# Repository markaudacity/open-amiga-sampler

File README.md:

# *ghOASt: a spectre is haunting open-source retro sampling*

## Open source schematics, parts lists and documentation for building a generic 8bit/mono Amiga parallel port sound sampler

*note: the following info is from the original repo and I claim no credit for it* 

Amiga parallel port sound samplers are simple hardware devices from the late 80s/early 90s which allowed users to digitally record audio to their home computer and represented a revolution in DIY music production. They were once cheap and ubiquitous, but they're increasingly expensive and hard to find as the popularity of retro computing continues to rise.

OAS is an open source PCB and case design for a cartridge-style mono sampler geared towards use with Soundtracker and Protracker-style software. It is easy to make, cheap to produce, and thanks to its built in preamp with hardware gain control it can deliver higher quality results than the average vintage sampler.

Check out the Wiki for answers to most hardware questions:
## [OAS Wiki](https://github.com/echolevel/open-amiga-sampler/wiki)

### Background
***
* [What are Amiga samplers?](https://github.com/echolevel/open-amiga-sampler/wiki/What-are-Amiga-samplers%3F)
* [Why build more?](https://github.com/echolevel/open-amiga-sampler/wiki/Why-build-more%3F)

### Development

***
* [How do they work?](https://github.com/echolevel/open-amiga-sampler/wiki/How-do-they-work%3F)
* [⚠️ WARNING](https://github.com/echolevel/open-amiga-sampler/wiki/%E2%9A%A0%EF%B8%8F-WARNING)
* [That WARNING sounds serious. How did you test your design without risking Amiga hardware?](https://github.com/echolevel/open-amiga-sampler/wiki/That-WARNING-sounds-serious.-How-did-you-test-your-design-without-risking-your-Amiga-hardware%3F)
* [Why is this sampler design mono, not stereo?](https://github.com/echolevel/open-amiga-sampler/wiki/Why-is-this-sampler-design-mono,-not-stereo%3F)
* [What's the aim in terms of quality and application?](https://github.com/echolevel/open-amiga-sampler/wiki/What's-the-aim-in-terms-of-quality-and-application%3F)
* [What about those edge cases? Who is OAS not aimed at?](https://github.com/echolevel/open-amiga-sampler/wiki/What-about-those-edge-cases%3F-Who-is-OAS-not-aimed-at%3F)
* [How compatible is OAS with existing software? (Work in progress, submissions welcome)](https://github.com/echolevel/open-amiga-sampler/wiki/How-compatible-is-OAS-with-existing-software%3F-(Work-in-progress,-submissions-welcome))
* [Current status](https://github.com/echolevel/open-amiga-sampler/wiki/Current-status)

### Production & Availability

***
* [Availability](https://github.com/echolevel/open-amiga-sampler/wiki/Availability)
* [DIY assembly](https://github.com/echolevel/open-amiga-sampler/wiki/DIY-assembly)

### Appendices

***
* [Appendix A: Sample rates deep-dive](https://github.com/echolevel/open-amiga-sampler/wiki/Appendix-A:-Sample-rates-deep-dive)
* [Appendix B: Sampling duration deep-dive](https://github.com/echolevel/open-amiga-sampler/wiki/Appendix-B:-Sampling-duration-deep-dive)

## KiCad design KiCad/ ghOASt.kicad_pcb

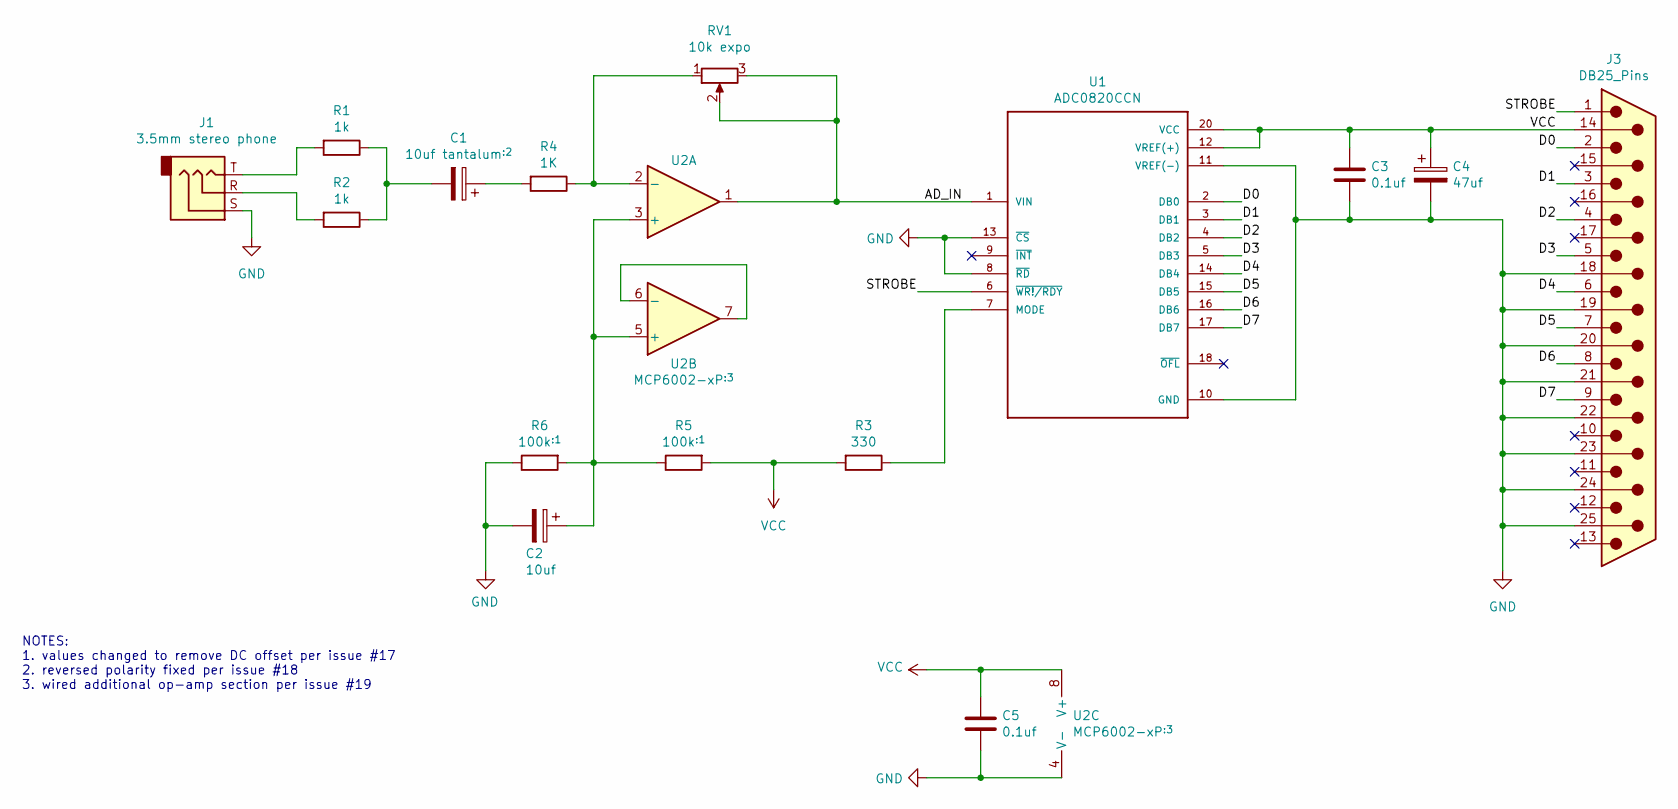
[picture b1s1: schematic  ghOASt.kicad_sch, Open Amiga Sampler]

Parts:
C1: 10uf tantalum^{:2}; CP_Radial_D4.0mm_P1.50mm
C2: 10uf; CP_Radial_D4.0mm_P1.50mm
C3, C5: 0.1uf; C_Disc_D4.3mm_W1.9mm_P5.00mm
C4: 47uf; CP_Radial_D4.0mm_P1.50mm
J1: 3.5mm stereo phone; Jack_3.5mm_CUI_SJ1-3543
J3: DB25_Pins; DSUB-25_Male_EdgeMount_P2.77mm
R1, R2: 1k; R_Axial_DIN0207_L6.3mm_D2.5mm_P10.16mm_Horizontal
R3: 330; R_Axial_DIN0207_L6.3mm_D2.5mm_P10.16mm_Horizontal
R4: 1K; R_Axial_DIN0207_L6.3mm_D2.5mm_P10.16mm_Horizontal
R5, R6: 100k^{:1}; R_Axial_DIN0207_L6.3mm_D2.5mm_P10.16mm_Horizontal
RV1: 10k expo; Potentiometer_Alpha_RD901F-40-00D_Single_Vertical
U1: ADC0820CCN; DIP-20_W7.62mm_Socket
U2: MCP6002-xP^{:3}; DIP-8_W7.62mm_Socket

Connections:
/AD_IN: RV1.2, RV1.3, U1.1 (VIN), U2.1
/D0: J3.2, U1.2 (DB0)
/D1: J3.3, U1.3 (DB1)
/D2: J3.4, U1.4 (DB2)
/D3: J3.5, U1.5 (DB3)
/D4: J3.6, U1.14 (DB4)
/D5: J3.7, U1.15 (DB5)
/D6: J3.8, U1.16 (DB6)
/D7: J3.9, U1.17 (DB7)
/STROBE: J3.1, U1.6 (~WR!/RDY)
GND: C2.2, C3.2, C4.2, C5.2, J1.S, J3.18, J3.19, J3.20, J3.21, J3.22, J3.23, J3.24, J3.25, R6.1, U1.8 (~RD), U1.10 (GND), U1.11 (VREF(-)), U1.13 (~CS), U2.4 (V-)
unnamed: C1.1, R4.2
unnamed: C1.2, R1.1, R2.1
unnamed: J1.R, R2.2
unnamed: J1.T, R1.2
unnamed: R3.1, U1.7 (MODE)
unnamed: C2.1, R5.1, R6.2, U2.3 (+), U2.5 (+)
unnamed: R4.1, RV1.1, U2.2 (-)
unnamed: U2.6 (-), U2.7
VCC: C3.1, C4.1, C5.1, J3.14, R3.2, R5.2, U1.12 (VREF(+)), U1.20 (VCC), U2.8 (V+)

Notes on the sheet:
NOTES: 1. values changed to remove DC offset per issue #17 2. reversed polarity fixed per issue #18 3. wired additional op-amp section per issue #19

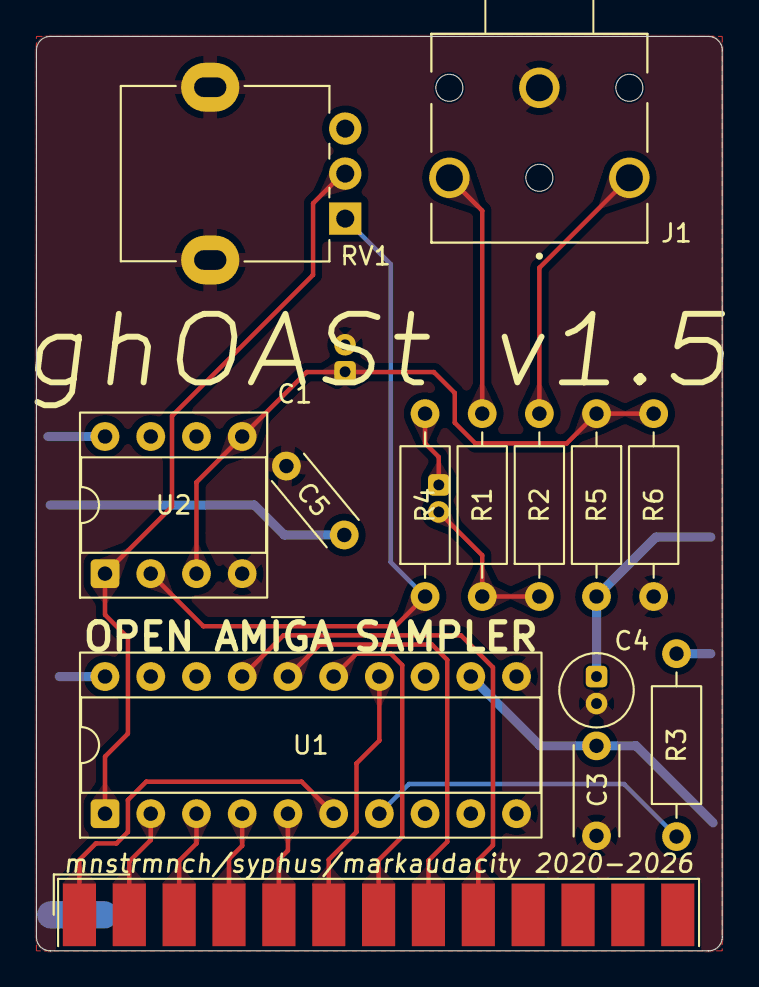
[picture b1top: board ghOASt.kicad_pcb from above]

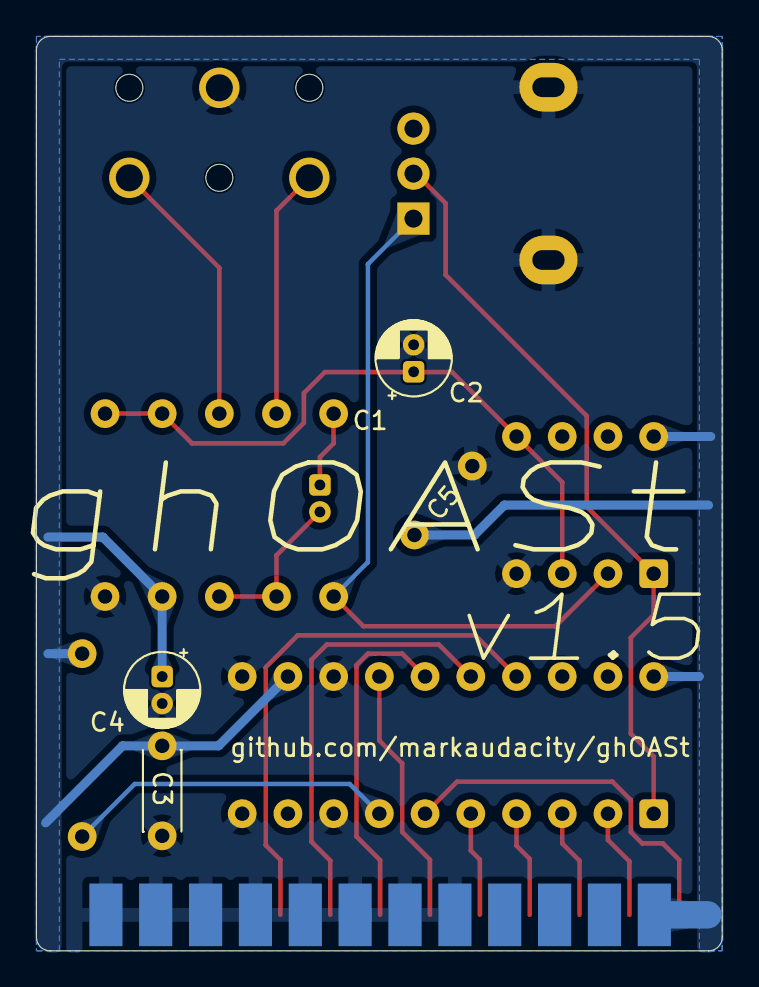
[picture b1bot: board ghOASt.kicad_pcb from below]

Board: 2 copper layers, 38.1 x 50.8 mm, 16 parts (5 on the bottom side), 20 nets.

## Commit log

2026-06-16 streamlined schematic, added mods up to 1.1
2026-06-16 major update to PCB
    removed unnecessary traces and vias, re-routed everything, added footprints for gain pot and 3.5mm phone jack soldered direct to board
    Lots of KiCad project cleanup: added netclasses, adjusted design rules, changed global labels to local (since the schematic only has one page) and unified the schematic so it is no longer in several 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
2026-06-16 tweaks, edits, embedded models
2026-06-17 fixing some sync oopsies
2026-06-17 renaming
2026-06-17 rearrange
